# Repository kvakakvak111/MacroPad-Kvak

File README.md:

**Inspiration:**

    My Friend showed me his MacroPad and i was amazed. I wanted to make my own and better one :) 

**Challenges**

    Making the PCB in KiCAD was extremly dificult for me. I never used to work with these. But it was pretty fun when I got into it. Modeling the case was pretty okey, I followed the guide on blueprint.hackclub.com and made a good case. Maybe I will edit the case later.

**BOM:**

    9x Cherry MX switches
    9x blank DSA keycaps
    1x Seeed XIAO RP2040 (THT)
    1x PCB
    4x M3 x 7mm screws

    Others:
    KMK firmware
    Top and Bottom step file of Case.

Images:

| Case          | Schematic     | PCB  |
| ----------- |:-----------:| --------|
|  | |  |

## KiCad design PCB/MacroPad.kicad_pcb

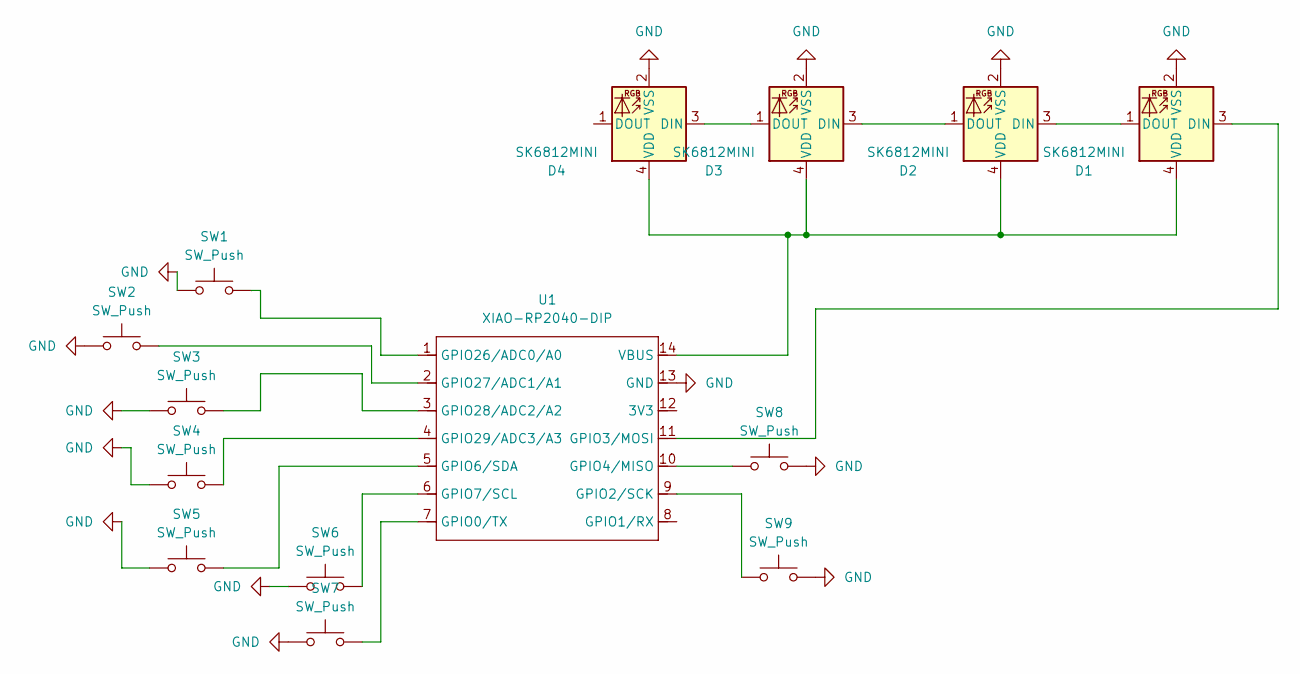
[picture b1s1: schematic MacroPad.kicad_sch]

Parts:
D1, D2, D3, D4: SK6812MINI; SK6812MINI-E_fixed
SW1, SW2, SW3, SW4, SW5, SW6, SW7, SW8, SW9: SW_Push; SW_Cherry_MX_1.00u_PCB
U1: XIAO-RP2040-DIP

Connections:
GND: D1.2 (VSS), D2.2 (VSS), D3.2 (VSS), D4.2 (VSS), SW1.1, SW2.1, SW3.1, SW4.1, SW5.1, SW6.1, SW7.1, SW8.2, SW9.2, U1.13 (GND)
unnamed: D1.3 (DIN), U1.11 (GPIO3/MOSI)
unnamed: D1.1 (DOUT), D2.3 (DIN)
unnamed: D1.4 (VDD), D2.4 (VDD), D3.4 (VDD), D4.4 (VDD), U1.14 (VBUS)
unnamed: D2.1 (DOUT), D3.3 (DIN)
unnamed: D3.1 (DOUT), D4.3 (DIN)
unnamed: SW7.2, U1.7 (GPIO0/TX)
unnamed: SW9.1, U1.9 (GPIO2/SCK)
unnamed: SW8.1, U1.10 (GPIO4/MISO)
unnamed: SW5.2, U1.5 (GPIO6/SDA)
unnamed: SW6.2, U1.6 (GPIO7/SCL)
unnamed: SW1.2, U1.1 (GPIO26/ADC0/A0)
unnamed: SW2.2, U1.2 (GPIO27/ADC1/A1)
unnamed: SW3.2, U1.3 (GPIO28/ADC2/A2)
unnamed: SW4.2, U1.4 (GPIO29/ADC3/A3)

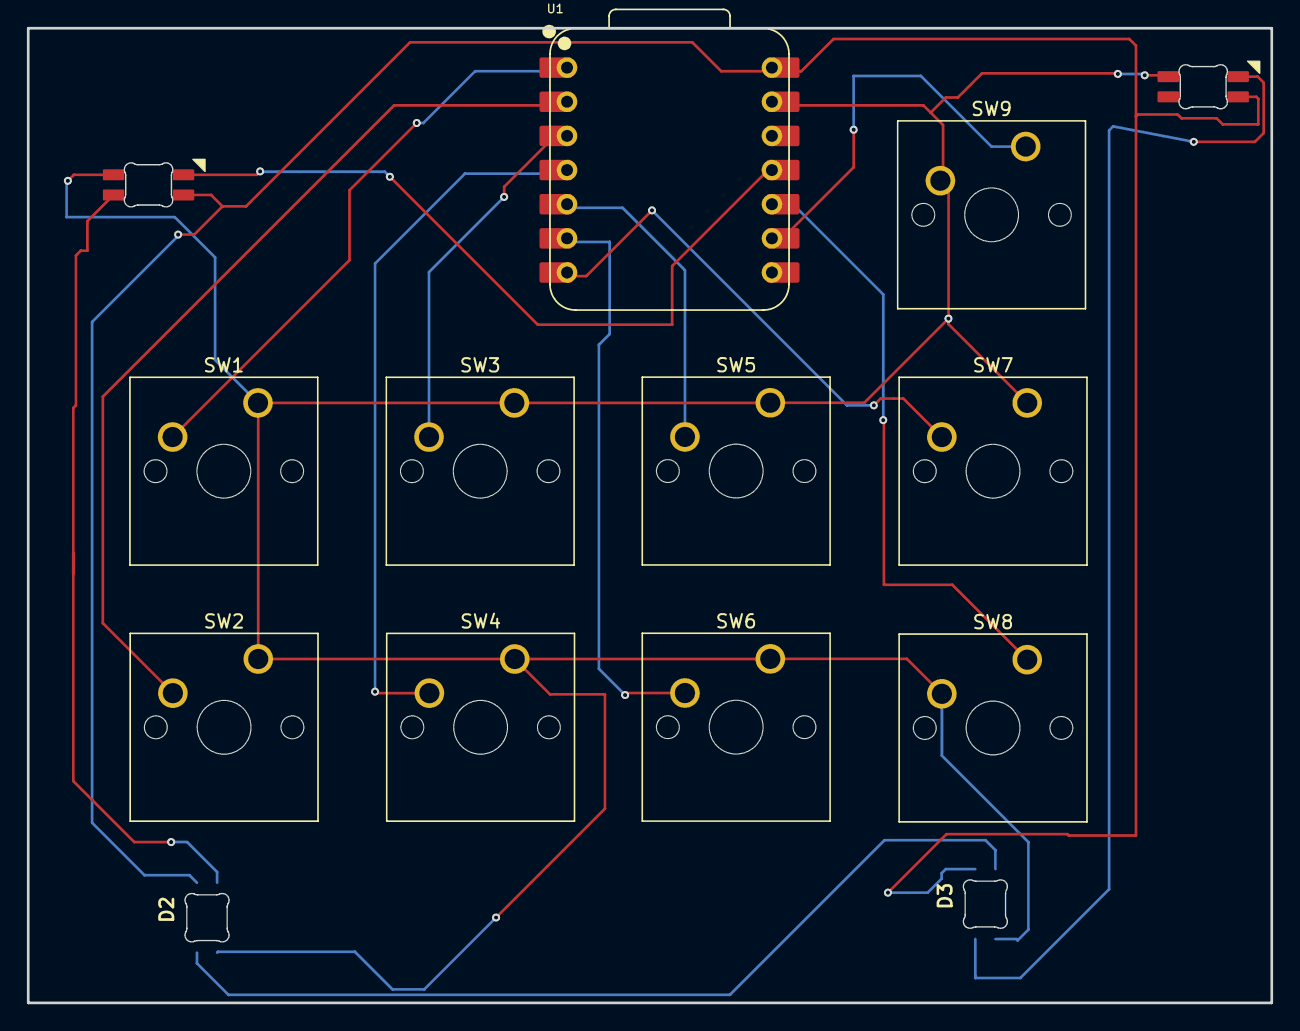
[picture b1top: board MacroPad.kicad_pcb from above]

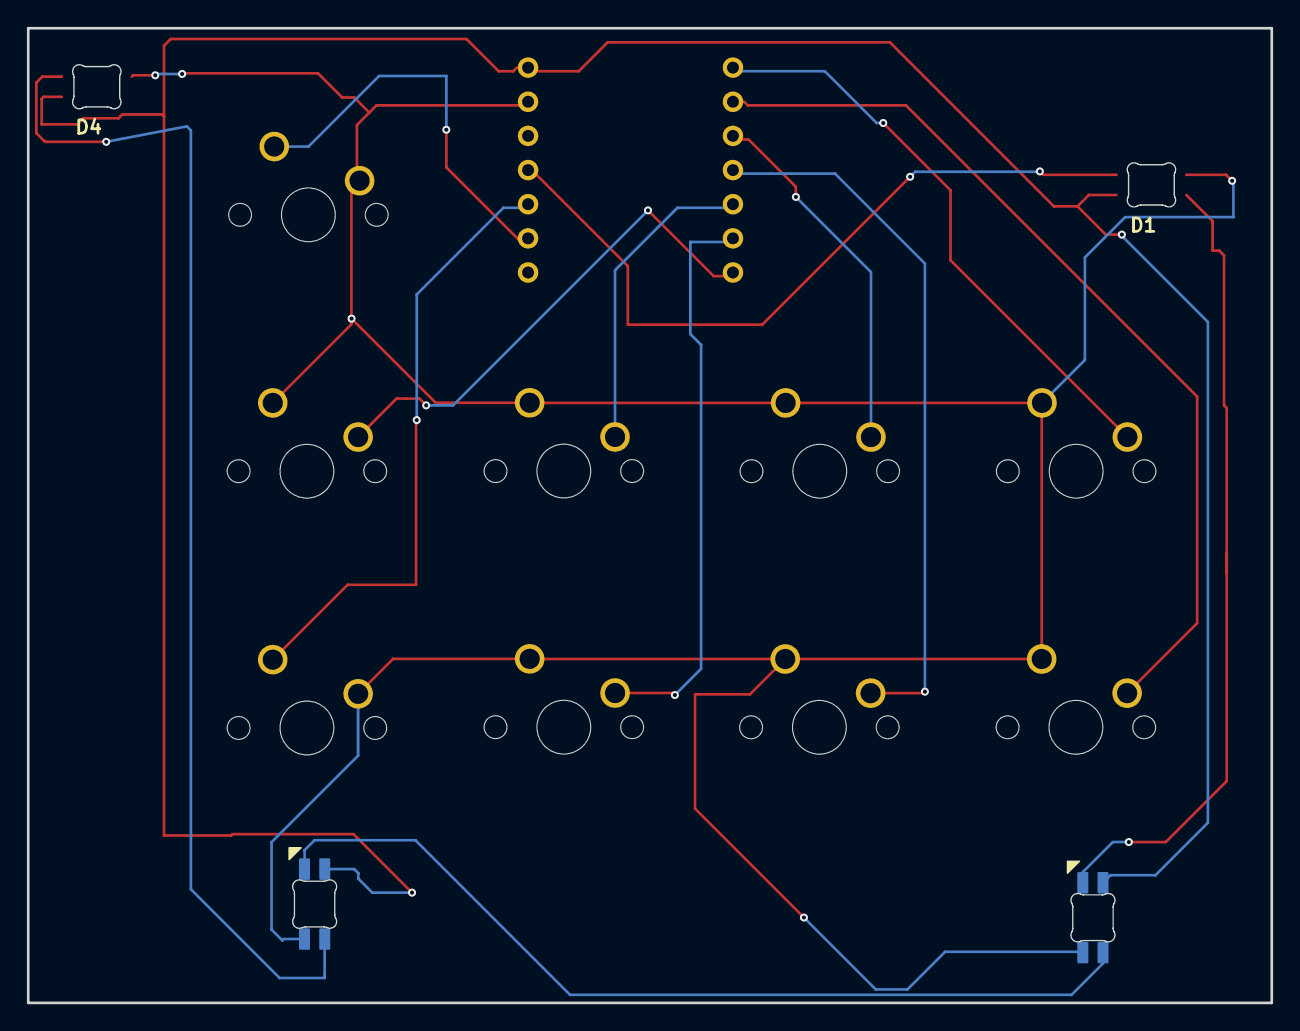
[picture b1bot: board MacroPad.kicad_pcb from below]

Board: 2 copper layers, 92.5 x 72.5 mm, 14 parts (2 on the bottom side), 15 nets.

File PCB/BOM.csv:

"Reference","Qty","Value","DNP","Exclude from BOM","Exclude from Board","Footprint","Datasheet"
"D1,D2,D3,D4","4","SK6812MINI","","","","footprints:SK6812MINI-E_fixed","https://cdn-shop.adafruit.com/product-files/2686/SK6812MINI_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"
"SW1,SW2,SW3,SW4,SW5,SW6,SW7,SW8,SW9","9","SW_Push","","","","Button_Switch_Keyboard:SW_Cherry_MX_1.00u_PCB","~"
"U1","1","XIAO-RP2040-DIP","","","","Seeed Studio XIAO Series Library:XIAO-RP2040-DIP",""

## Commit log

2025-12-30 Created firs upload of all files
2025-12-30 added iages of shcemtic and pcb
